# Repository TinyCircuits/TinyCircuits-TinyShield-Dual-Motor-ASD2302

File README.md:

# TinyCircuits TinyShield Dual Motor Board
# ASD2302 Rev3

The design files are located under design_files/ for the TinyCircuits ASD2302 Rev 3 PCB.  This is a TinyShield board (Square Version, 20mm x 20mm) that has a two TI DRV8847 motor drivers on it, to allow two DC brushed motors to be driven.

Format is in Cadsoft Eagle format - Eagle version 6.2 was used for the original design.

For more infomation on this, check out the product page at TinyCircuits.com:  https://tinycircuits.com/collections/motors/products/dual-motor-tinyshield

# License:

Design by TinyCircuits.
All design files are released under the Creative Commons Attribution Share-Alike 3.0 License, see the following link for details: http://creativecommons.org/licenses/by-sa/3.0

All text above must be included in any redistribution or derived design

This project uses designs and concepts developed as part of the Arduino project and the LilyPad project.  The TinyCircuits design files themselves (schematics, PCB and libraries) are not directly derived from these works' design files and have been created new, however the concepts and basic architecture behind the TinyDuino and TinyLily products are derived and we thank the hard work of the organizations below for their contributions to open-source hardware:
  
Original Arduino Uno Design by Team Arduino

LilyPad Arduino Design by Leah Buechley and Sparkfun Electronics

Please support the open-source hardware community

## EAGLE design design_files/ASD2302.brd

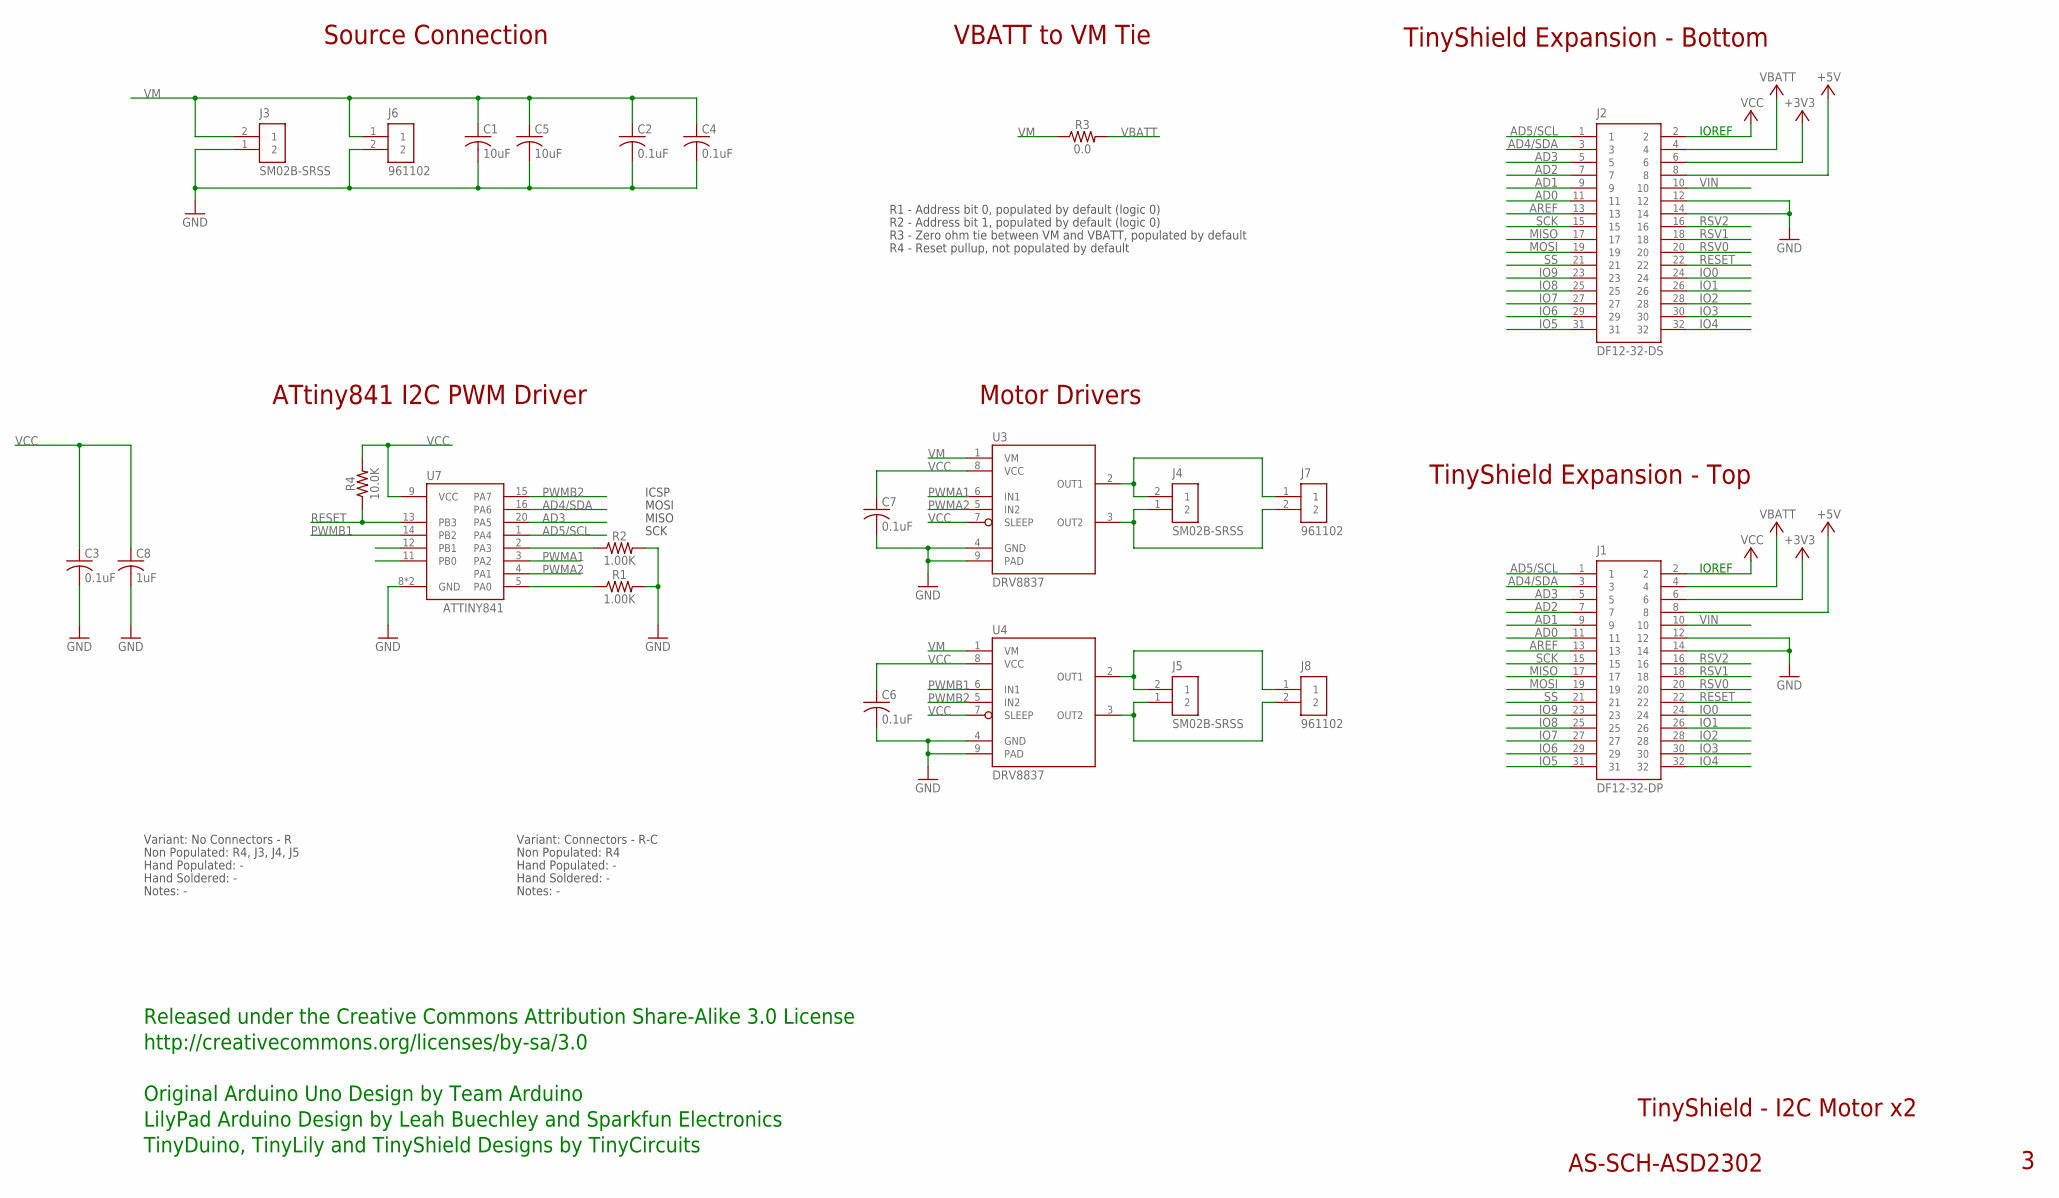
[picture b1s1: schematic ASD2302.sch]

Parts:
C1, C5: 10uF; C0805
C2: 0.1uF; C0402
C3, C4, C6, C7: 0.1uF; C0402; PARTNO AS-ITM-00008
C8: 1uF; C0402; PARTNO AS-ITM-00105
J1: DF12-32-DP; PARTNO AS-ITM-00015
J2: DF12-32-DS; PARTNO AS-ITM-00012
J3, J4, J5: SM02B-SRSS; JST_SH_2X1
J6, J7, J8: 961102; 2X.1"
R1, R2: 1.00K; 0402; PARTNO AS-ITM-00003
R3: 0.0; 0402
R4: 10.0K; 0402
U3, U4: DRV8837; WSON-8
U7: ATTINY841; VQFN-20

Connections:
+3V3: J1.6, J2.6
+5V: J1.8, J2.8
AD0: J1.11, J2.11
AD1: J1.9, J2.9
AD2: J1.7, J2.7
AD3: J1.5, J2.5, U7.20 (PA5)
AD4/SDA: J1.3, J2.3, U7.16 (PA6)
AD5/SCL: J1.1, J2.1, U7.1 (PA4)
AREF: J1.13, J2.13
GND: C1.2, C2.2, C3.2, C4.2, C5.2, C6.2, C7.2, C8.2, J1.12, J1.14, J2.12, J2.14, J3.1 (2), J6.2, R1.2, R2.2, U3.4 (GND), U3.9 (PAD), U4.4 (GND), U4.9 (PAD), U7.8 (GND), U7.PAD (GND)
IO0: J1.24, J2.24
IO1: J1.26, J2.26
IO2: J1.28, J2.28
IO3: J1.30, J2.30
IO4: J1.32, J2.32
IO5: J1.31, J2.31
IO6: J1.29, J2.29
IO7: J1.27, J2.27
IO8: J1.25, J2.25
IO9: J1.23, J2.23
MISO: J1.17, J2.17
MOSI: J1.19, J2.19
unnamed: J5.1 (2), J8.2, U4.3 (OUT2)
unnamed: J5.2 (1), J8.1, U4.2 (OUT1)
unnamed: J4.2 (1), J7.1, U3.2 (OUT1)
unnamed: J4.1 (2), J7.2, U3.3 (OUT2)
unnamed: R2.1, U7.2 (PA3)
unnamed: R1.1, U7.5 (PA0)
PWMA1: U3.6 (IN1), U7.3 (PA2)
PWMA2: U3.5 (IN2), U7.4 (PA1)
PWMB1: U4.6 (IN1), U7.14 (PB2)
PWMB2: U4.5 (IN2), U7.15 (PA7)
RESET: J1.22, J2.22, R4.1, U7.13 (PB3)
RSV0: J1.20, J2.20
RSV1: J1.18, J2.18
RSV2: J1.16, J2.16
SCK: J1.15, J2.15
SS: J1.21, J2.21
VBATT: J1.4, J2.4, R3.2
VCC: C3.1, C6.1, C7.1, C8.1, J1.2, J2.2, R4.2, U3.7 (SLEEP), U3.8 (VCC), U4.7 (SLEEP), U4.8 (VCC), U7.9 (VCC)
VIN: J1.10, J2.10
VM: C1.1, C2.1, C4.1, C5.1, J3.2 (1), J6.1, R3.1, U3.1 (VM), U4.1 (VM)

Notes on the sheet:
TinyShield Expansion - Bottom
TinyShield - I2C Motor x2
AS-SCH-ASD2302
TinyShield Expansion - Top
IOREF
Released under the Creative Commons Attribution Share-Alike 3.0 License
http://creativecommons.org/licenses/by-sa/3.0
LilyPad Arduino Design by Leah Buechley and Sparkfun Electronics
TinyDuino, TinyLily and TinyShield Designs by TinyCircuits
Original Arduino Uno Design by Team Arduino
ATtiny841 I2C PWM Driver
Motor Drivers
VBATT to VM Tie
Source Connection
MOSI
MISO
SCK
ICSP
R1 - Address bit 0, populated by default (logic 0)
R2 - Address bit 1, populated by default (logic 0)
R3 - Zero ohm tie between VM and VBATT, populated by default
R4 - Reset pullup, not populated by default
Non Populated: R4, J3, J4, J5
Hand Populated: -
Hand Soldered: -
Notes: -
Variant: No Connectors - R
Non Populated: R4
Variant: Connectors - R-C

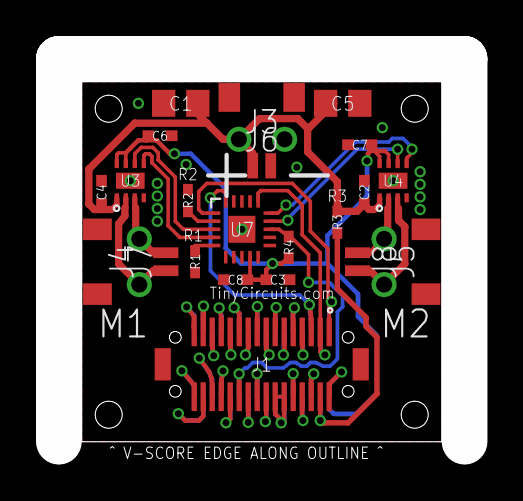
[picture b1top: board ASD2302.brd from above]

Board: 2 copper layers, 20.0 x 20.0 mm, 24 parts (1 on the bottom side), 42 nets.

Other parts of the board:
U$1: DOCFIELD-TINYCIRCUITS-PCB

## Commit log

2015-07-30 :confetti_ball: Added .gitattributes & .gitignore files
2019-01-04 Update format
2019-05-10 add zip file
2019-05-10 new image
2019-05-21 pics
2019-05-22 added images
2019-05-23 updated images
2019-05-24 cleaned sketch
2019-10-17 fix program
2020-01-24 update program
2020-02-11 image update
2020-07-28 Add CAD data
2020-08-14 Update CAD drawing
2020-10-05 remove old version examples
